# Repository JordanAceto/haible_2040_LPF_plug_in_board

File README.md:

# NOTE: development of all VCF plug-in boards has been moved here https://github.com/JordanAceto/VCF_plug_in_boards
### This repo will no longer be updated. Follow the above link for the most current files.

# Discrete SSM2040 LPF Plug-In Board 

Small low pass filter PCB, designed to plug into a larger motherboard. This discrete SSM2040 filter implementation is based on notes from the late Jurgen Haible. Thank you for all your wonderful contributions Jurgen.

## Details

Four pole LPF with Q compensation. This PCB includes the audio path and CV inputs for frequency and feedback, but does not include any modulation sources.

The intended use for this board is to plug in to a larger motherboard which contains slots for two of these plug-in boards, as well as modulation sources, panel controls, and input/output routing. This motherboard could accept different filter boards sharing this footprint and header layout, for realizing stereo effects of various flavors.

## Inputs

-Audio in: dry audio input to be filtered.

-Frequency CV in: 0 volts to +2.048 volts, higher voltage = higher sweep.

-Feedback CV in: 0 volts to +2.048 volts, higher voltage = more feedback.

## Outputs

-Audio out: filtered audio output.

## Power Supply Requirements

A bipolar 12 volt power supply is required. This will typically come from the motherboard.

## Calibration

-RV1 (depth trim): trims the depth of incoming frequency CV signals. Turn CW for greater depth and CCW for less depth. Adjust to taste.

-RV2 (center trim): trims the center frequency of the filter. Turn CW for higher center frequency and CCW for lower center frequency. Adjust to taste.

-RV3 (feedback trim): trims the maximum amount of feedback. Turn CW for more maximum feedback and CCW for less maximum feedback. Exercise caution when adjusting this, as extreme settings can result in loud oscillations which could damage your ears or speakers if you are monitoring the sound with a loud amplifier. If you set this trimmer to be right on the edge of oscillation when about +2 volts is applied to the feedback CV input then make sure to sweep the frequency through its entire range, as a setting that doesn't squeal at certain frequency settings may squeal at other settings.

## Parts Ordering
The BOM has a link to a Mouser project.

Gerbers can be generated from the kicad_docs.

## License
CC by 4.0

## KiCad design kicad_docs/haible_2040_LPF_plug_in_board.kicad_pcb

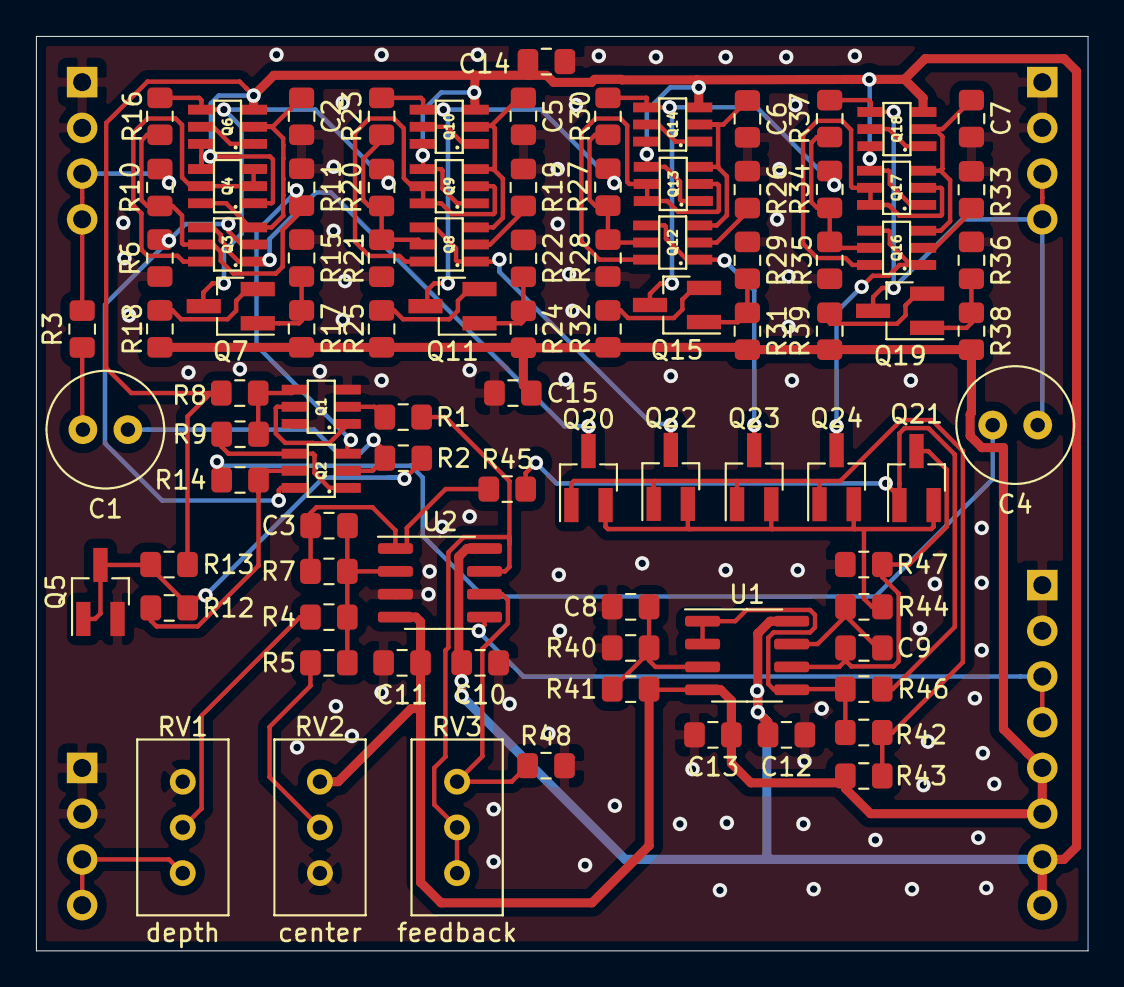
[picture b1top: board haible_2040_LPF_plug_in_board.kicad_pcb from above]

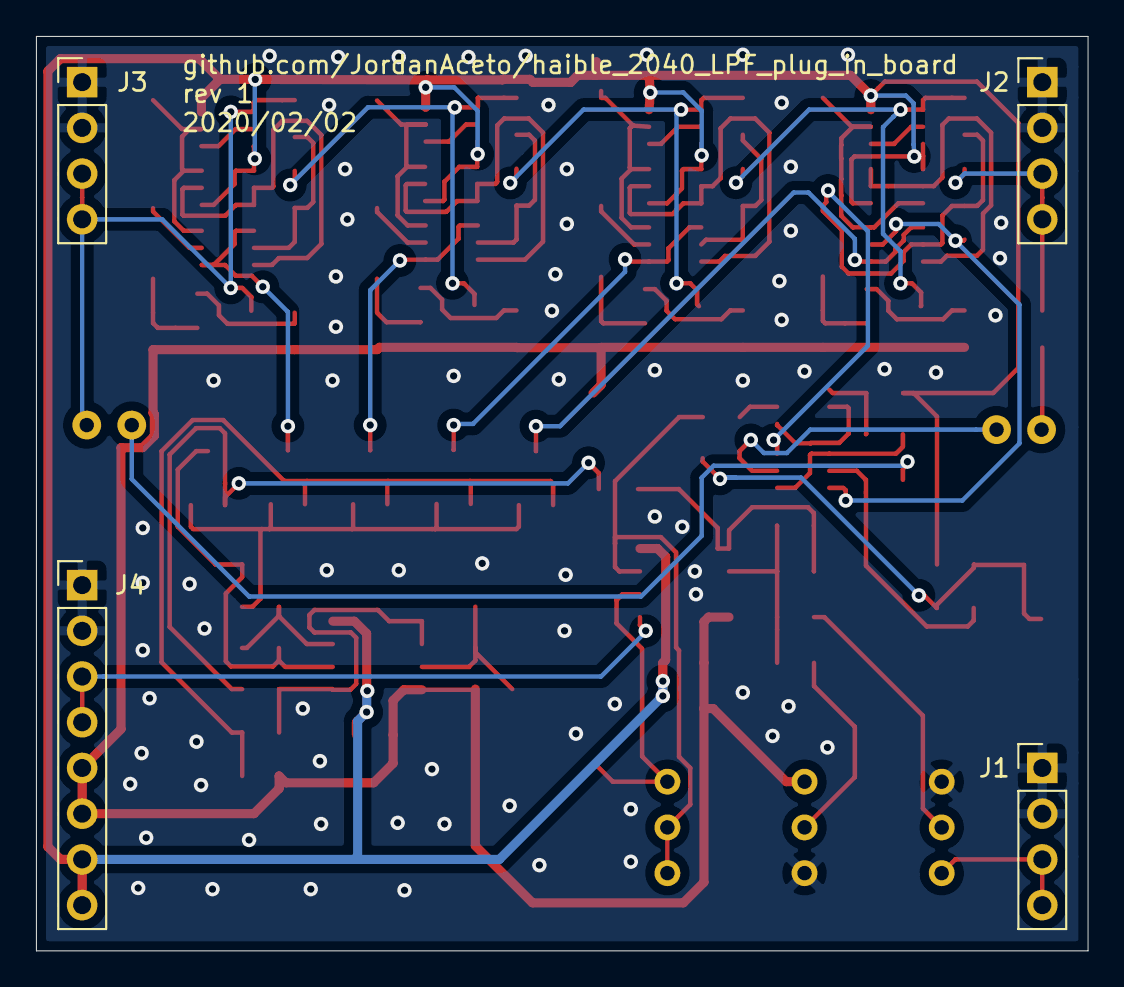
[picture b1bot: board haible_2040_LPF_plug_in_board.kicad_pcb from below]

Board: 2 copper layers, 58.4 x 50.8 mm, 96 parts (4 on the bottom side), 64 nets.

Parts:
C1, C4: 10uF; C_Radial_D6.3mm_H11.0mm_P2.50mm
C2, C5, C6, C7: 1nF; C_0805_2012Metric_Pad1.15x1.40mm_HandSolder
C3: 470pF; C_0805_2012Metric_Pad1.15x1.40mm_HandSolder
C8: 22uF; C_0805_2012Metric_Pad1.15x1.40mm_HandSolder
C9: 2n2; C_0805_2012Metric_Pad1.15x1.40mm_HandSolder
C10, C11, C12, C13, C14, C15: 100nF; C_0805_2012Metric_Pad1.15x1.40mm_HandSolder
J1, J2, J3: Conn_01x04_Male; PinHeader_1x04_P2.54mm_Vertical
J4: Conn_01x08_Male; PinHeader_1x08_P2.54mm_Vertical
Q1, Q2, Q4, Q9, Q13, Q17: BCM857DS; SOT457
Q3, Q6, Q8, Q10, Q12, Q14, Q16, Q18: BCM847DS; SOT457
Q5, Q7, Q11, Q15, Q19, Q20, Q21, Q22, Q23, Q24: BC847; SOT-23_Handsoldering
R1, R2, R12, R46: 1k; R_0805_2012Metric_Pad1.15x1.40mm_HandSolder
R3, R45: 51k; R_0805_2012Metric_Pad1.15x1.40mm_HandSolder
R4, R47: 100k; R_0805_2012Metric_Pad1.15x1.40mm_HandSolder
R5, R7: 560k; R_0805_2012Metric_Pad1.15x1.40mm_HandSolder
R6, R11, R19, R21, R26, R28, R33, R35: 220; R_0805_2012Metric_Pad1.15x1.40mm_HandSolder
R8: 3k3; R_0805_2012Metric_Pad1.15x1.40mm_HandSolder
R9: 15k; R_0805_2012Metric_Pad1.15x1.40mm_HandSolder
R10, R16, R20, R23, R27, R30, R34, R37: 10k; R_0805_2012Metric_Pad1.15x1.40mm_HandSolder
R13, R17, R24, R31, R38, R40: 12k; R_0805_2012Metric_Pad1.15x1.40mm_HandSolder
R14: 20k; R_0805_2012Metric_Pad1.15x1.40mm_HandSolder
R15, R22, R29, R36, R41: 120k; R_0805_2012Metric_Pad1.15x1.40mm_HandSolder
R18, R25, R32, R39: 1k2; R_0805_2012Metric_Pad1.15x1.40mm_HandSolder
R42: 100; R_0805_2012Metric_Pad1.15x1.40mm_HandSolder
R43: 180k; R_0805_2012Metric_Pad1.15x1.40mm_HandSolder
R44: 2k2; R_0805_2012Metric_Pad1.15x1.40mm_HandSolder
R48: 27k; R_0805_2012Metric_Pad1.15x1.40mm_HandSolder
RV1: 10k; Potentiometer_Bourns_3296W_Vertical
RV2, RV3: 100k; Potentiometer_Bourns_3296W_Vertical
U1, U2: TL072; SOIC-8_3.9x4.9mm_P1.27mm

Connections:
+12V: C10.1, C12.1, C14.1, J4.7, J4.8, Q4.1, Q4.4, Q6.3, Q6.6, Q9.1, Q9.4, Q10.3, Q10.6, Q13.1, Q13.4, Q14.3, Q14.6, Q17.1, Q17.4, Q18.3, Q18.6, R8.1, R13.1, U1.8, U2.8
-12V: C11.2, C13.2, C15.2, J4.5, J4.6, R17.2, R18.2, R24.2, R25.2, R31.2, R32.2, R38.2, R39.2, R41.2, R43.1, RV2.1, U1.4, U2.4
/FB_CV: R1.2, RV3.2, RV3.3, U2.7
/LP_stage_1/FB_signal_in: C4.1, J3.3, J3.4, Q18.4, Q19.3, R37.1
/LP_stage_1/LP_in_1: J2.3, J2.4, R3.2, R10.2
/LP_stage_1/bias_current_in_1: Q3.1, Q3.4, Q20.3
/LP_stage_2/LP_in_2: Q6.4, Q7.3, R16.1, R20.2
/LP_stage_2/bias_current_in_2: Q8.1, Q8.4, Q22.3
/LP_stage_3/LP_in_3: Q10.4, Q11.3, R23.1, R27.2
/LP_stage_3/bias_current_in_3: Q12.1, Q12.4, Q23.3
/LP_stage_4/LP_in_4: Q14.4, Q15.3, R30.1, R34.2
/LP_stage_4/bias_current_in_4: Q16.1, Q16.4, Q24.3
/bias_current_gen/CV_in: C3.2, R7.2, R45.1, U2.1
GND: C2.2, C5.2, C6.2, C7.2, C8.1, C10.2, C11.1, C12.2, C13.1, C14.2, C15.1, J1.1, J1.2, J2.1, J2.2, J3.1, J3.2, J4.1, J4.2, Q1.3, Q1.6, Q5.2, R6.2, R11.2, R15.1, R19.2, R21.2, R22.1, R26.2, R28.2, R29.1, R33.2, R35.2, R36.1, R40.1, R47.1, R48.2, RV1.1, RV2.3, U2.3
unnamed: C1.1, Q2.2, R2.2
unnamed: C1.2, R3.1
unnamed: C2.1, Q3.3, Q4.6, Q6.2
unnamed: C3.1, R4.2, R5.2, R7.1, U2.2
unnamed: C4.2, R14.1
unnamed: C5.1, Q8.3, Q9.3, Q10.2
unnamed: C6.1, Q12.3, Q13.3, Q14.2
unnamed: C7.1, Q16.3, Q17.3, Q18.2
unnamed: C8.2, R40.2, R41.1, U1.3
unnamed: C9.1, Q21.3, R47.2, U1.6
unnamed: C9.2, R44.1, U1.7
unnamed: J1.3, J1.4, RV1.3
unnamed: J4.3, J4.4, U2.5
unnamed: Q1.1, Q1.5
unnamed: Q1.2, R1.1
unnamed: Q1.4, R8.2, R9.1
unnamed: Q2.1, Q2.4, R9.2
unnamed: Q2.3, Q3.5, R10.1, R11.1, R16.2
unnamed: Q2.5, R12.2, R14.2
unnamed: Q2.6, Q3.2, R6.1
unnamed: Q3.6, Q4.2, Q4.3, Q4.5
unnamed: Q5.1, Q5.3, R2.1, R12.1, R13.2
unnamed: Q6.1, Q6.5
unnamed: Q7.1, R15.2, R17.1
unnamed: Q7.2, R18.1
unnamed: Q8.2, R19.1
unnamed: Q8.5, R20.1, R21.1, R23.2
unnamed: Q8.6, Q9.2, Q9.5, Q9.6
unnamed: Q10.1, Q10.5
unnamed: Q11.1, R22.2, R24.1
unnamed: Q11.2, R25.1
unnamed: Q12.2, R26.1
unnamed: Q12.5, R27.1, R28.1, R30.2
unnamed: Q12.6, Q13.2, Q13.5, Q13.6
unnamed: Q14.1, Q14.5
unnamed: Q15.1, R29.2, R31.1
unnamed: Q15.2, R32.1
unnamed: Q16.2, R33.1
unnamed: Q16.5, R34.1, R35.1, R37.2
unnamed: Q16.6, Q17.2, Q17.5, Q17.6
unnamed: Q18.1, Q18.5
unnamed: Q19.1, R36.2, R38.1
unnamed: Q19.2, R39.1
unnamed: Q20.1, Q22.1, Q23.1, Q24.1, R42.2, R43.2
unnamed: Q20.2, Q21.2, Q22.2, Q23.2, Q24.2, R44.2
unnamed: Q21.1, R45.2, R46.2
unnamed: R4.1, RV1.2
unnamed: R5.1, RV2.2
unnamed: R42.1, R46.1, U1.1, U1.2, U1.5
unnamed: R48.1, RV3.1, U2.6

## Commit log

2020-02-02 split schem into pages, redo pcb
2020-02-02 add schematic pdf
2020-02-02 clean up accidental ods lock file
2020-02-02 tidy up pcb
2020-02-02 add pics dir
2020-02-02 fix rear pcb view pic
2020-02-02 add preliminary readme
2020-02-02 Create LICENSE
2020-08-01 update readme to link to new repo
